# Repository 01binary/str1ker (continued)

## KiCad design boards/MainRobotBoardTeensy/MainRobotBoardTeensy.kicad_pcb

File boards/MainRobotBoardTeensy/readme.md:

# Main Robot Board

A board that controls robot head & body and measures voltage/current/battery charge.

+ Head Pan/Tilt
+ Torso Pan/Tilt
+ Mouth Movement
+ Voltage and Current Sensing

## Modules

The following components are placed onto the board as modules:

|Module|Function|
|-|-|
|[Teensy 4.1](https://www.sparkfun.com/teensy-4-1.html)|[ROS](https://www.ros.org/) Node|
|[ACS37220 Current Sensor 100A](https://www.pololu.com/product/5295)|Bus Current Sensing|
|[SSD1306 OLED Displays](https://www.amazon.com/dp/B00O2LKEW2)|Monochrome 0.96" 128x64 Voltage/Current/Power displays|
|[B10 1B4PG3Y2R](https://www.amazon.com/dp/B0C9QGMGFB)|Battery Charge Meter|
## Devices

The following external components are connected to the board via JST-XH locking connectors:

|Device|Function|
|-|-|
|[TB6600HG Stepper Motor Driver](https://www.amazon.com/dp/B01N6AIEQT)|Head Pan Motor|
|`4x` [Mini IBT Motor Driver](https://www.aliexpress.us/item/2251832603816751.html)|`2x` Head Tilt Motor Driver, `2x` Torso Tilt Motor Driver|
|`2x` Hollow Shaft Potentiometers|Head Tilt Encoder, Torso Tilt Encoder|
|[PerfectPass 56Kg Servo](https://www.amazon.com/dp/B09Y4NZJBJ)|Mouth Movement|
|[CPM-MCVC-3441S-RLN](https://teknic.com/model-info/CPM-MCVC-3441S-RLN/?model_voltage=75VDC)|Torso Pan Integrated Motor Driver

## Buses

|Bus|Device|Address
|-|-|-|
|`I2C`|SSD1306 voltage, current, and power meter displays|`0x3C`, `0x3D`|

## Pins

|Pin|Function
|-|-|
| `D14/A0`  | `ACS37220` Current Sensor `VOUT`
| `D15/A1`  | Head Tilt Potentiometer `SIG`
| `D16/A2`  | Torso Tilt Potentiometer `SIG`
| `D17/A3`  | Voltage Sense `SIG`
| `D19` | I2C `SCL` (SSD1306 x2)
| `D18` | I2C `SDA` (SSD1306 x2)
| `D0` | `TB6600` Head Pan Stepper Driver `EN`
| `D1` | `TB6600` Head Pan Stepper Driver `DIR`
| `D2` | `TB6600` Head Pan Stepper Driver `PUL`
| `D3` | `CPM-MCVC-3441S-RLN` Torso Motor `EN`
| `D4` | `CPM-MCVC-3441S-RLN` Torso Motor `DIR` (A)
| `D5` | `CPM-MCVC-3441S-RLN` Torso Motor `PWM` (B)
| `D7` | Head Tilt Motor Driver 1 `EN`
| `D8` | Head Tilt Motor Driver 2 `EN`
| `D20` | Torso Tilt Motor Driver 1 `EN`
| `D21` | Torso Tilt Motor Driver 2 `EN`
| `D9` | Head Tilt Motor Driver 1 `LPWM`
| `D10` | Head Tilt Motor Driver 1 `RPWM`
| `D11` | Head Tilt Motor Driver 2 `LPWM`
| `D12` | Head Tilt Motor Driver 2 `RPWM`
| `D22` | Torso Tilt Motor Driver 1 `LPWM`
| `D23` | Torso Tilt Motor Driver 1 `RPWM`
| `D28` | Torso Tilt Motor Driver 2 `LPWM`
| `D29` | Torso Tilt Motor Driver 2 `RPWM`
| `D24` | Battery Level Meter `LED1` (Lowest Charge)
| `D25` | Battery Level Meter `LED2`
| `D26` | Battery Level Meter `LED3`
| `D27` | Battery Level Meter `LED4`
| `D30` | Battery Level Meter `LED5`
| `D31` | Battery Level Meter `LED6`
| `D32` | Battery Level Meter `LED7`
| `D33` | Battery Level Meter `LED8`
| `D34` | Battery Level Meter `LED9`
| `D35` | Battery Level Meter `LED10` (Highest Charge)
| `D36` | PerfectPass Servo `SIG`

## ROS Interface

The main-board Teensy is a rosserial node at `115200` baud. Its USB serial
port is reserved for ROS framing; the sketch does not print diagnostic text.

|Topic|Type|Direction|Rate / behavior|
|-|-|-|-|
|`main/command`|`str1ker/MainCommand`|Subscribe|Normalized `[-1, 1]` velocity commands for head pan/tilt and torso pan/tilt, plus mouth position in degrees. Motion stops if commands are absent for 500 ms.|
|`main/power`|`str1ker/PowerState`|Publish|Voltage (V), current (A), and power (W), at 10 Hz.|
|`main/battery`|`sensor_msgs/BatteryState`|Publish|LiFePO4 pack voltage, current, and estimated charge percentage, at 10 Hz.|
|`main/joint_states`|`sensor_msgs/JointState`|Publish|`head_tilt_joint`, `torso_tilt_joint`, and `mouth_joint` positions, at 10 Hz.|

The mouth servo is commanded to 90 degrees during startup. The two
potentiometer positions are currently normalized to `[0, 1]`; calibrate their
ADC endpoints and angular ranges in the firmware before treating them as
radians in a robot model. Head pan and torso pan are omitted from feedback
because this board has no position sensors for those axes.

## Bill of Materials

|Component|Description|
|-|-|
|[150080BS75000](https://www.digikey.com/en/products/detail/w%C3%BCrth-elektronik/)|Blue LED for `LPWM`/`RPWM` activity|
|[XL-1608SURC-06](https://www.lcsc.com/product-detail/C965799.html)|Red LED for `EN` status|
|[RC0603FR-0747RL](https://www.digikey.com/en/products/detail/yageo/rc0603fr-0747rl/727252)|`47R` Series Resistor (PWM channels)|
|[RC0603FR-07150RL](https://www.digikey.com/en/products/detail/yageo/RC0603FR-07150RL/726958)|`150R` Blue LED Resistor|
|[RC0603FR-07470RL](https://www.digikey.com/en/products/detail/yageo/RC0603FR-07470RL/727256)|`470R` Red LED and Battery Bar Segment Resistor|
|[RCG06031K00FKEA](https://www.digikey.com/en/products/detail/vishay-dale/rcg06031k00fkea/4172389)|`1K` Red LED Resistor|
|[RC0603FR-072K2L](https://www.digikey.com/en/products/detail/yageo/RC0603FR-072K2L/727016)|`2.2K` Series Resistor (ADC channels)|
|[CRCW060310K0FKEA](https://www.digikey.com/en/products/detail/vishay-dale/crcw060310k0fkea/1174782)|`10K` Pull-Down Resistor (PWM channels)|
|[0603WAF2202T5E](https://jlcpcb.com/partdetail/32812-0603WAF2202T5E/C31850)|`22K` Voltage Sense Divider Resistor|
|[CRCW0603100KFKEA](https://www.digikey.com/en/products/detail/vishay-dale/crcw0603100kfkea/1174896)|`100K` Pull-Dowh Resistor|
|[CL10B473KB8NNNC](https://www.digikey.com/en/products/detail/samsung-electro-mechanics/cl10b473kb8nnnc/3886721)|`47nF` Capacitor (ADC channels)|
|[SN74HC08DR](https://www.digikey.com/en/products/detail/texas-instruments/sn74hc08dr/276834)|IC Gate|
|[B10 1B4PG3Y2R](https://www.amazon.com/dp/B0C9QGMGFB)|LED Light Bar (Red/Blue/Green) with `DIP-20` Socket (Battery Charge Meter)|
|[AO3400A](https://www.digikey.com/en/products/detail/alpha-omega-semiconductor-inc/ao3400a/1855772)|LED Transistor|
|[TLC555CDR](https://www.digikey.com/en/products/detail/texas-instruments/tlc555cdr/276979)|555 Timer|
|[RC0603FR-07360KL](https://www.digikey.com/en/products/detail/yageo/rc0603fr-07360kl/727183)|555 Timer Resistor `360K`|
|[CC0603JRX7R7BB105](https://www.digikey.com/en/products/detail/yageo/CC0603JRX7R7BB105/7164369)|555 Timer Capacitor `1uF`|
|[C0402C103J4RACTU](https://www.digikey.com/en/products/detail/kemet/C0402C103J4RACTU/411041)|555 Timer Capacitor `0.01uF`|
|[CC0603KRX7R9BB104](https://www.digikey.com/en/products/detail/yageo/cc0603krx7r9bb104/2103082)|`100nF` Voltage Sense Capacitor|
|[74HCT125D,653](https://www.digikey.com/en/products/detail/nexperia-usa-inc/74hct125d-653/763113)|`3.3V` to `5V` Level Shifter|
|[JST_XH_B3B-XH-A](https://www.digikey.com/en/products/detail/jst-sales-america-inc/b3b-xh-a/1651046)|3-pin male receptacle for Head Tilt Potentiometer, Torso Tilt Potentiometer (`3V3`, `SIG`, `GND`), Head Tilt Driver, Torso Tilt Drivers (`LPWM`, `RPWM`, `EN`)|
|[JST_XH_B4B-XH-A](https://www.digikey.com/en/products/detail/jst-sales-america-inc/b4b-xh-a/1651047)|4-pin male receptacle for `TB6600` Driver (`3V3`, `PUL`, `DIR`, `ENA`)|
|[Molex 0702460802](https://www.digikey.com/en/products/detail/molex/0702460802/760180)|2-row 4-pin male receptacle for `CPM-MCVC-3441S-RLN` Driver (`EN+`, `EN-`, `A+`, `A-`, `B+`, `B-`, `ST+`, `ST-`)|
|[Teensy 4.1](https://www.sparkfun.com/teensy-4-1.html)|Teensy 4.1 without Headers|
|[ICM-648-1-GT-HT](https://www.digikey.com/en/products/detail/adam-tech/ICM-648-1-GT-HT/9832918)|Teensy IC DIP Socket, 48P|
|[Needle Headers](https://www.amazon.com/dp/B09WH8N3HX)|Teensy Needle Headers for DIP Socket|
|[ACS37220](https://www.pololu.com/product/5295)|Current Sensor `100A`, `3.3V` Logic|
|2x [SSD1306](https://www.amazon.com/dp/B00O2LKEW2)|Monochrome I2C OLED Displays `3.3V`|

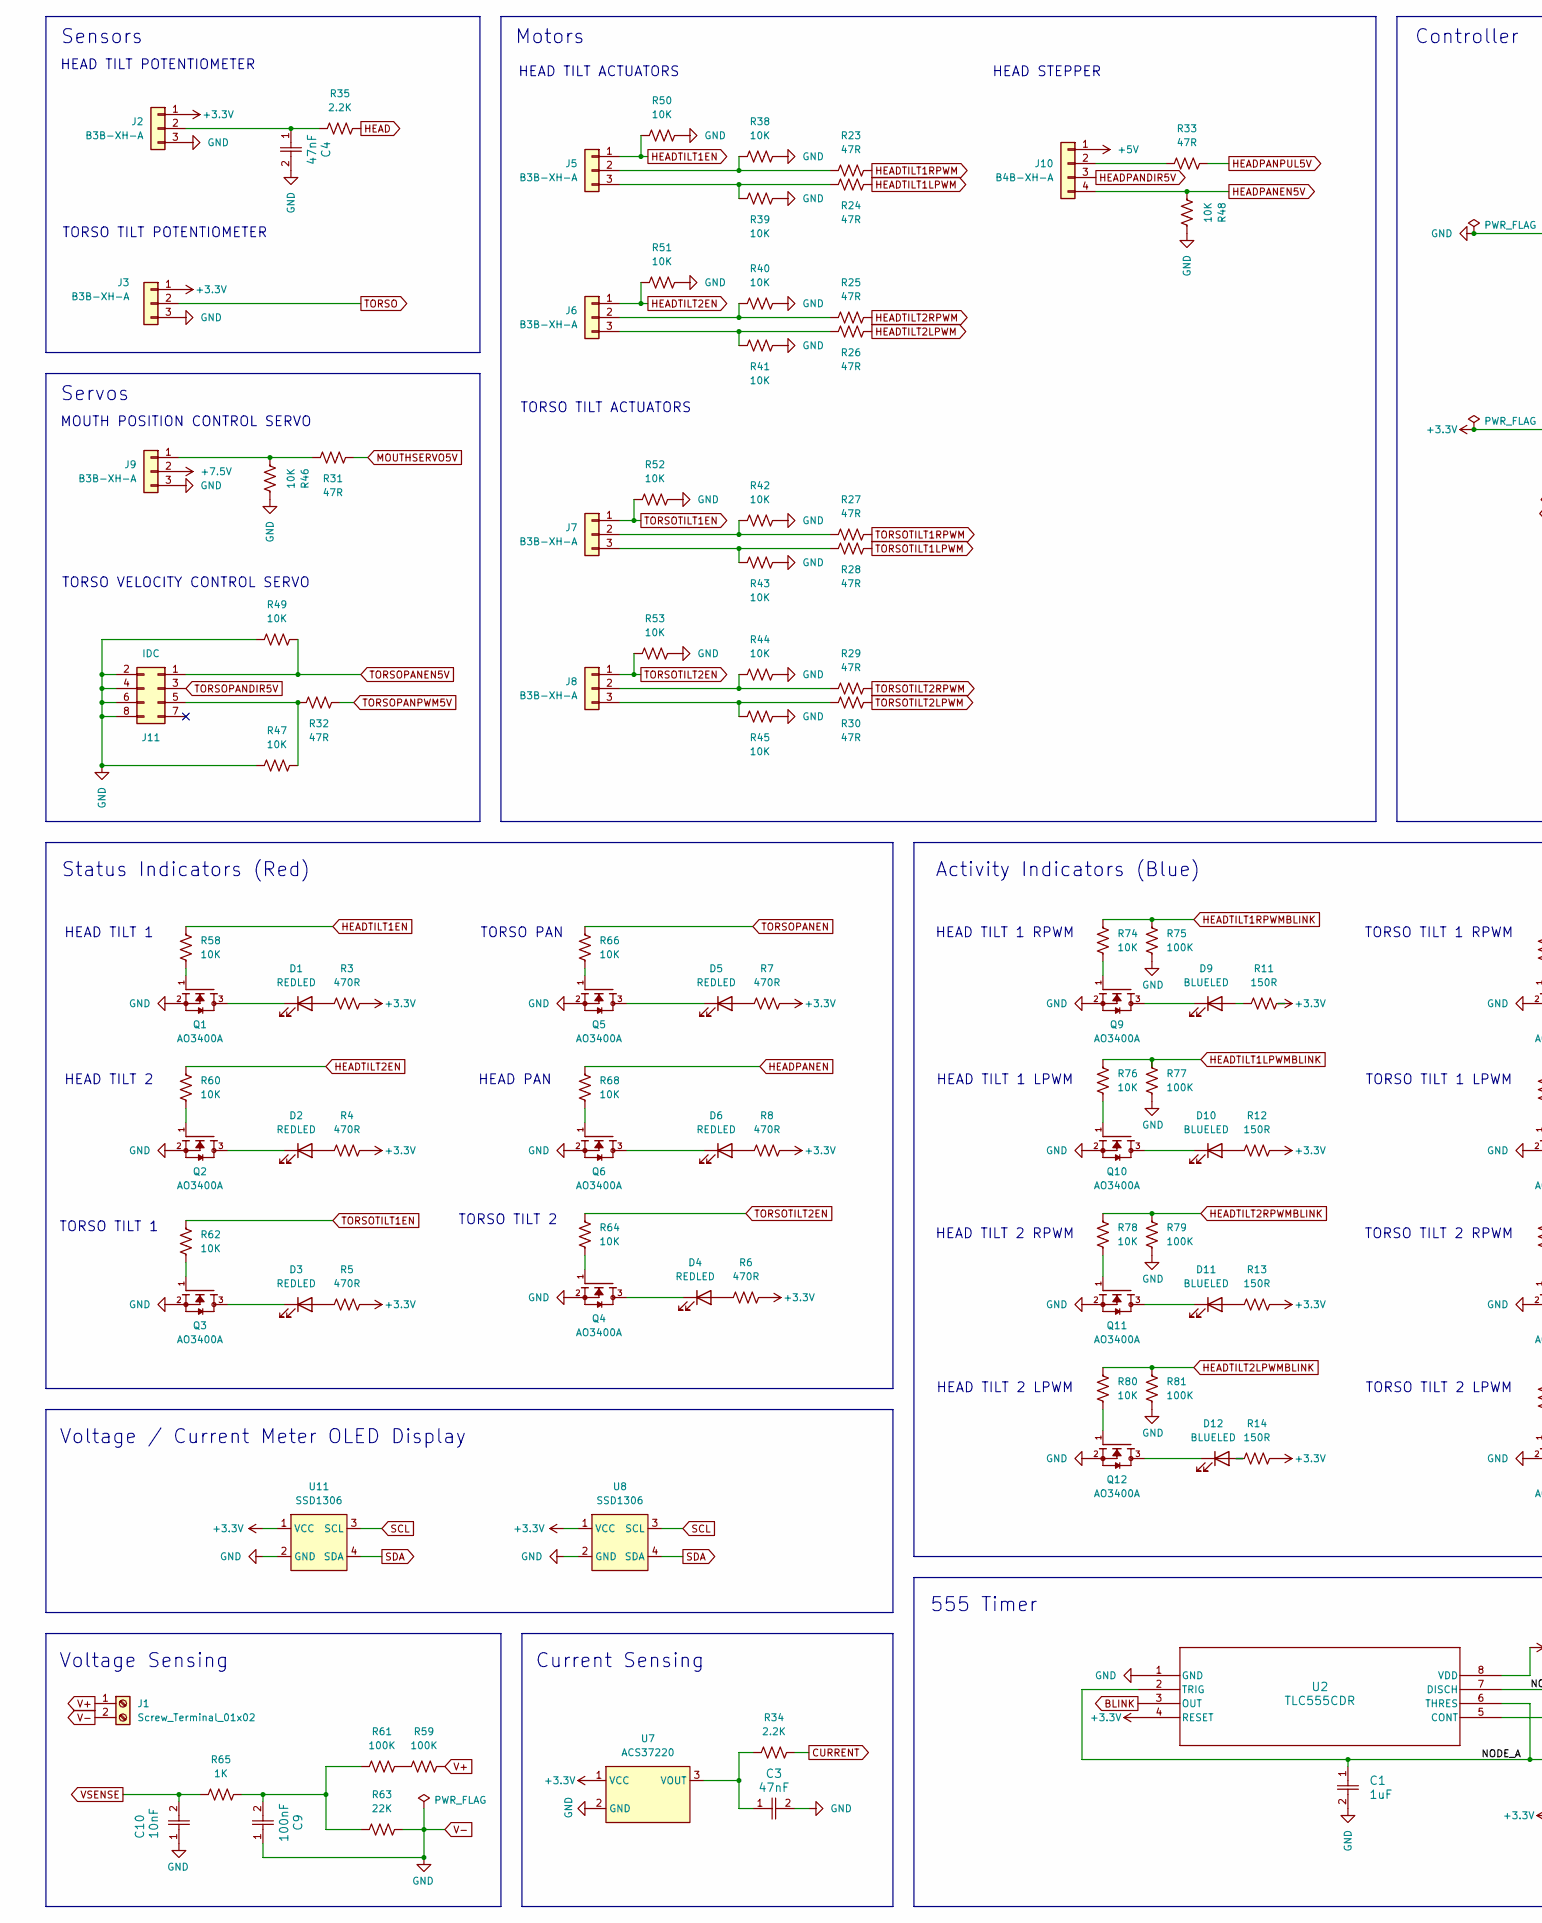
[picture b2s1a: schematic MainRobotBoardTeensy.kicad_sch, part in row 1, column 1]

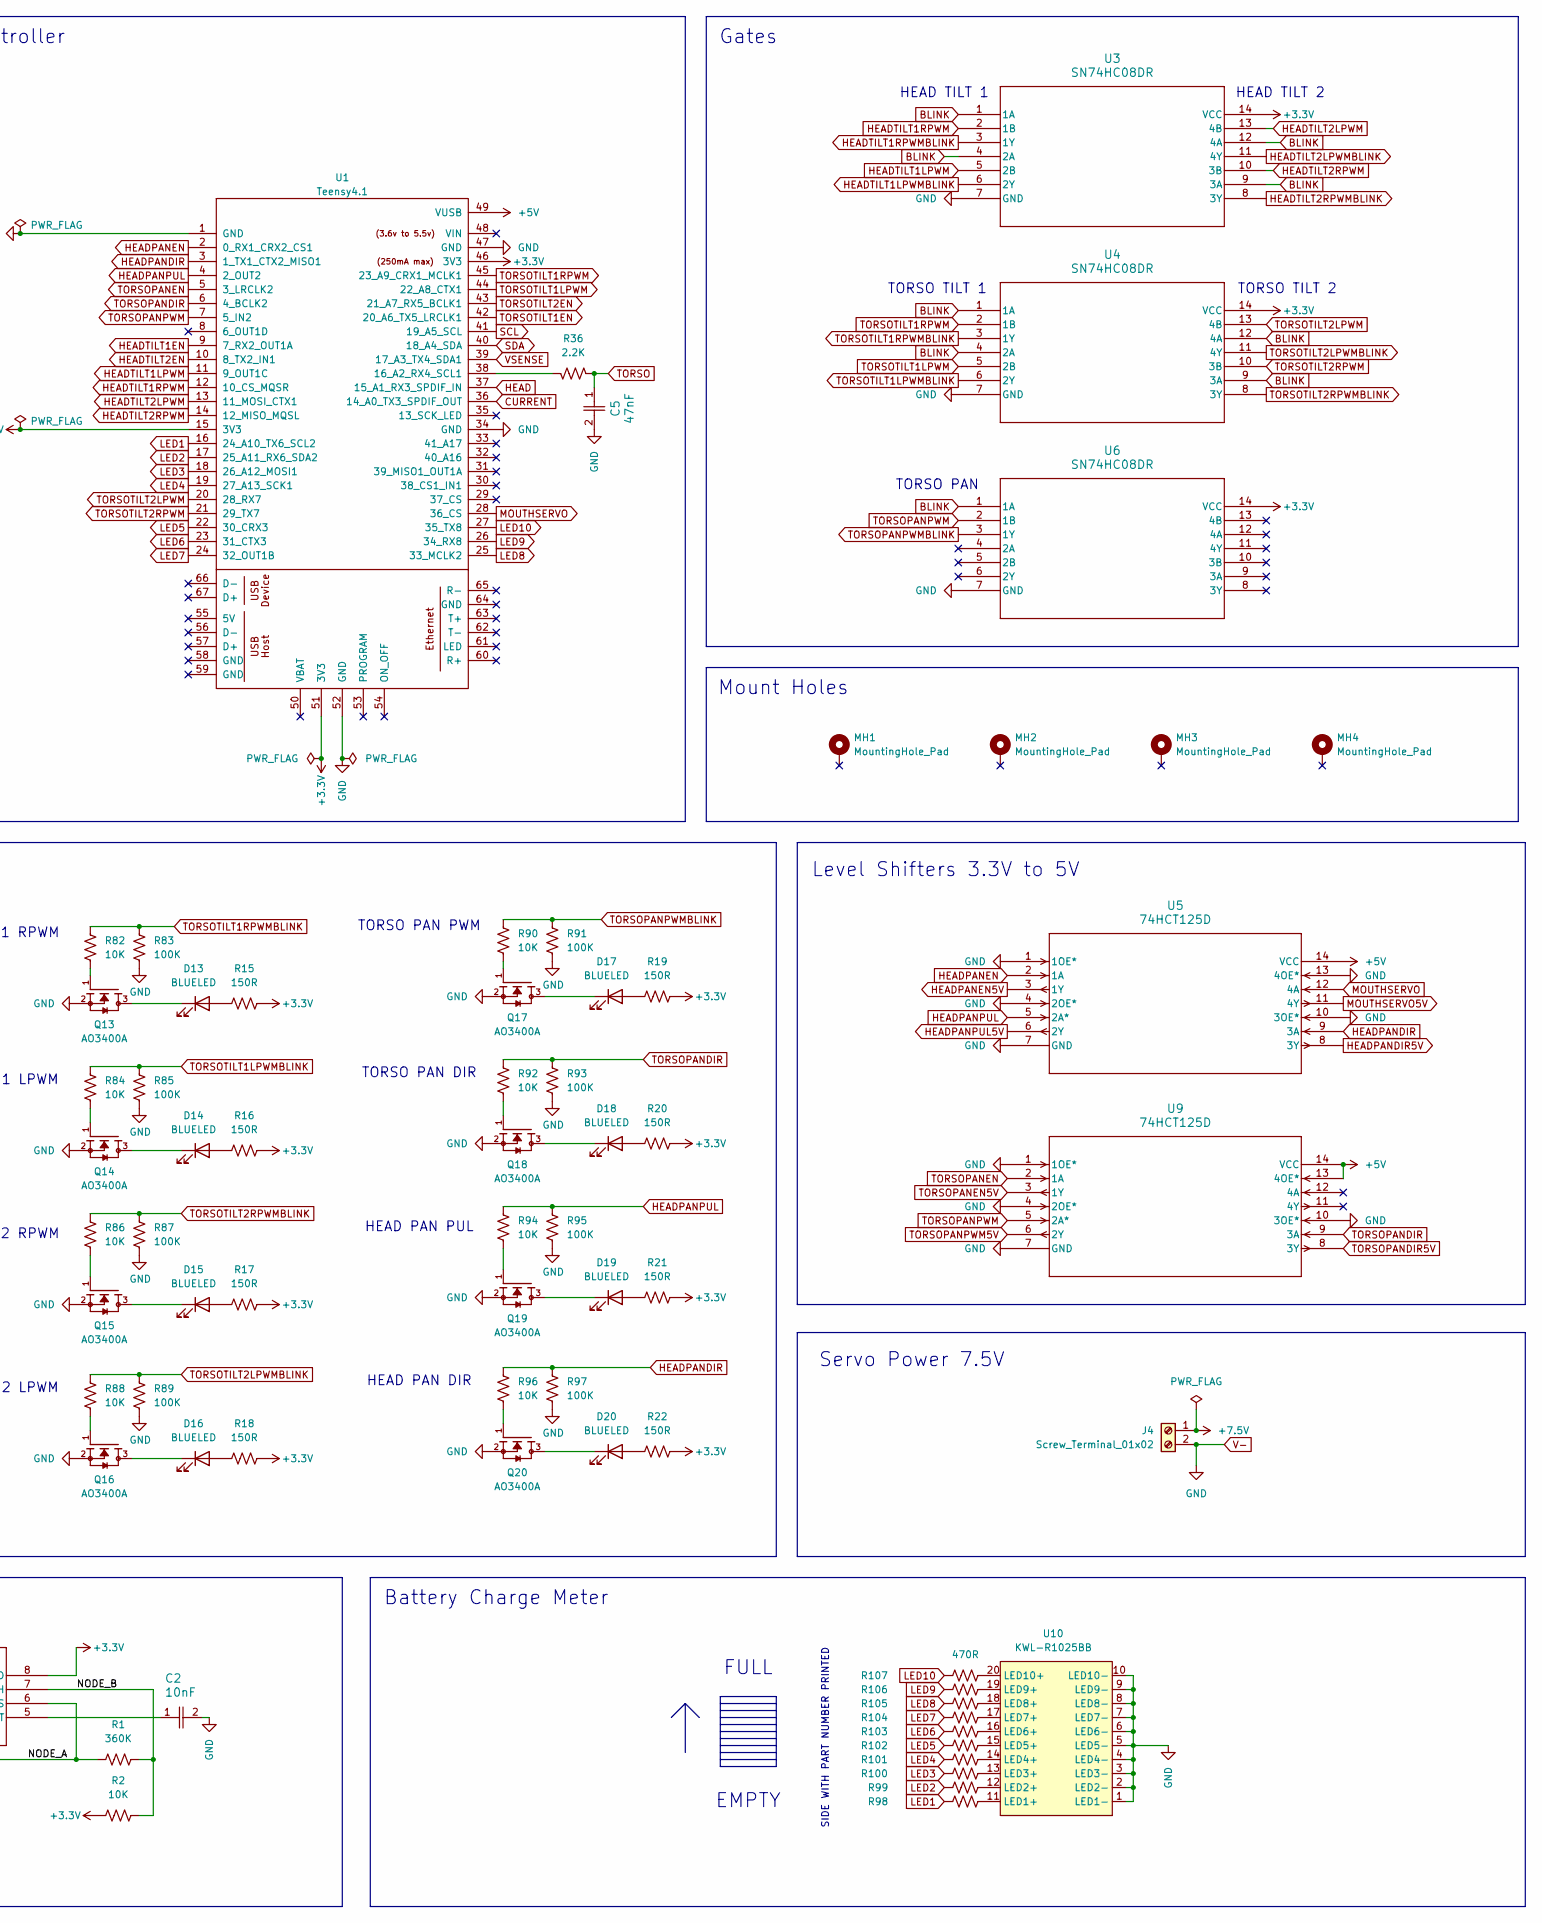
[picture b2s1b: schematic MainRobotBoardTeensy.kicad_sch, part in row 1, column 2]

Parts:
C1: 1uF; CC0603JRX7R7BB105; LCSC C519560
C2, C10: 10nF; C0402C103J4RACTU; LCSC C152817
C3, C4, C5: 47nF; CAPC1608X90N; LCSC C1622
C9: 100nF; CC0603KRX7R9BB104; LCSC C14663
D1, D2, D3, D4, D5, D6: REDLED; XL-1608SURC-06; LCSC C965799
D9, D10, D11, D12, D13, D14, D15, D16, D17, D18, D19, D20: BLUELED; 150080BS75000_Modified; LCSC C6067133
J1, J4: Screw_Terminal_01x02; TerminalBlock_Phoenix_MKDS-1,5-2-5.08_1x02_P5.08mm_Horizont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
J2, J3, J5, J6, J7, J8, J9: B3B-XH-A; JST_XH_B3B-XH-A_1x03_P2.50mm_Vertical
J10: B4B-XH-A; JST_XH_B4B-XH-A_1x04_P2.50mm_Vertical
J11: IDC; IDC-Header_2x04_P2.54mm_Vertical
MH1, MH2, MH3, MH4: MountingHole_Pad; MountingHole_3.2mm_M3_ISO7380_Pad
Q1, Q2, Q3, Q4, Q5, Q6, Q9, Q10, Q11, Q12, Q13, Q14, Q15, Q16, Q17, Q18, Q19, Q20: AO3400A; LCSC C20917
R1: 360K; RC0603FR-07360KL; LCSC C137740
R2, R38, R39, R40, R41, R42, R43, R44, R45, R46, R47, R48, R49, R50, R51, R52, R53, R58, R60, R62, R64, R66, R68, R74, R76, R78, R80, R82, R84, R86, R88, R90, R92, R94, R96: 10K; CRCW060310K0FKEA; LCSC C844918
R3, R4, R5, R6, R7, R8, R98, R99, R100, R101, R102, R103, R104, R105, R106, R107: 470R; RC0603FR-07470RL; LCSC C114669
R11, R12, R13, R14, R15, R16, R17, R18, R19, R20, R21, R22: 150R; RESC1607X60N; LCSC C114608
R23, R24, R25, R26, R27, R28, R29, R30, R31, R32, R33: 47R; RESC1608X55; LCSC C114623
R34, R35, R36: 2.2K; RC0603FR-072K2L; LCSC C114662
R59, R61, R75, R77, R79, R81, R83, R85, R87, R89, R91, R93, R95, R97: 100K; CRCW0603100KFKEA; LCSC C844916
R63: 22K; 0603WAF2202T5E; LCSC C31850
R65: 1K; RCG06031K00FKEA; LCSC C4264491
U1: Teensy4.1; Teensy41
U2: TLC555CDR; LCSC C6986
U3, U4, U6: SN74HC08DR; LCSC C337768
U5, U9: 74HCT125D
U7: ACS37220
U8, U11: SSD1306
U10: KWL-R1025BB

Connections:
+3.3V: J2.1, J3.1, R2.1, R3.2, R4.2, R5.2, R6.2, R7.2, R8.2, R11.2, R12.2, R13.2, R14.2, R15.2, R16.2, R17.2, R18.2, R19.2, R20.2, R21.2, R22.2, U1.15 (3V3), U1.46 (3V3), U1.51 (3V3), U2.4 (RESET), U2.8 (VDD), U3.14 (VCC), U4.14 (VCC), U6.14 (VCC), U7.1 (VCC), U8.1 (VCC), U11.1 (VCC)
+5V: J10.1, U1.49 (VUSB), U5.14 (VCC), U9.13 (4OE*), U9.14 (VCC)
+7.5V: J4.1, J9.2
/NODE_A: C1.1, R1.1, U2.2 (TRIG), U2.6 (THRES)
/NODE_B: R1.2, R2.2, U2.7 (DISCH)
BLINK: U2.3 (OUT), U3.1 (1A), U3.4 (2A), U3.9 (3A), U3.12 (4A), U4.1 (1A), U4.4 (2A), U4.9 (3A), U4.12 (4A), U6.1 (1A)
CURRENT: R34.2, U1.36 (14_A0_TX3_SPDIF_OUT)
HEAD: R35.2, U1.37 (15_A1_RX3_SPDIF_IN)
HEADPANDIR: R96.1, R97.1, U1.3 (1_TX1_CTX2_MISO1), U5.9 (3A)
HEADPANDIR5V: J10.3, U5.8 (3Y)
HEADPANEN: R68.1, U1.2 (0_RX1_CRX2_CS1), U5.2 (1A)
HEADPANEN5V: J10.4, R48.1, U5.3 (1Y)
HEADPANPUL: R94.1, R95.1, U1.4 (2_OUT2), U5.5 (2A*)
HEADPANPUL5V: R33.2, U5.6 (2Y)
HEADTILT1EN: J5.1, R50.1, R58.1, U1.9 (7_RX2_OUT1A)
HEADTILT1LPWM: R24.2, U1.11 (9_OUT1C), U3.5 (2B)
HEADTILT1LPWMBLINK: R76.1, R77.1, U3.6 (2Y)
HEADTILT1RPWM: R23.2, U1.12 (10_CS_MQSR), U3.2 (1B)
HEADTILT1RPWMBLINK: R74.1, R75.1, U3.3 (1Y)
HEADTILT2EN: J6.1, R51.1, R60.1, U1.10 (8_TX2_IN1)
HEADTILT2LPWM: R26.2, U1.13 (11_MOSI_CTX1), U3.13 (4B)
HEADTILT2LPWMBLINK: R80.1, R81.1, U3.11 (4Y)
HEADTILT2RPWM: R25.2, U1.14 (12_MISO_MQSL), U3.10 (3B)
HEADTILT2RPWMBLINK: R78.1, R79.1, U3.8 (3Y)
LED1: R98.2, U1.16 (24_A10_TX6_SCL2)
LED2: R99.2, U1.17 (25_A11_RX6_SDA2)
LED3: R100.2, U1.18 (26_A12_MOSI1)
LED4: R101.2, U1.19 (27_A13_SCK1)
LED5: R102.2, U1.22 (30_CRX3)
LED6: R103.2, U1.23 (31_CTX3)
LED7: R104.2, U1.24 (32_OUT1B)
LED8: R105.2, U1.25 (33_MCLK2)
LED9: R106.2, U1.26 (34_RX8)
LED10: R107.2, U1.27 (35_TX8)
MOUTHSERVO: U1.28 (36_CS), U5.12 (4A)
MOUTHSERVO5V: R31.2, U5.11 (4Y)
unnamed: C9.2, R61.1, R63.1, R65.2
unnamed: D1.2 (A), R3.1
unnamed: D1.1 (K), Q1.3
unnamed: D2.2 (A), R4.1
unnamed: D2.1 (K), Q2.3
unnamed: D3.2 (A), R5.1
unnamed: D3.1 (K), Q3.3
unnamed: D4.2 (A), R6.1
unnamed: D4.1 (K), Q4.3
unnamed: D5.2 (A), R7.1
unnamed: D5.1 (K), Q5.3
unnamed: D6.2 (A), R8.1
unnamed: D6.1 (K), Q6.3
unnamed: D9.2 (A), R11.1
unnamed: D9.1 (K), Q9.3
unnamed: D10.2 (A), R12.1
unnamed: D10.1 (K), Q10.3
unnamed: D11.2 (A), R13.1
unnamed: D11.1 (K), Q11.3
unnamed: D12.2 (A), R14.1
unnamed: D12.1 (K), Q12.3
unnamed: D13.2 (A), R15.1
unnamed: D13.1 (K), Q13.3
unnamed: D14.2 (A), R16.1
unnamed: D14.1 (K), Q14.3
unnamed: D15.2 (A), R17.1
unnamed: D15.1 (K), Q15.3
unnamed: D16.2 (A), R18.1
unnamed: D16.1 (K), Q16.3
unnamed: D17.2 (A), R19.1
unnamed: D17.1 (K), Q17.3
unnamed: D18.2 (A), R20.1
unnamed: D18.1 (K), Q18.3
unnamed: D19.2 (A), R21.1
unnamed: D19.1 (K), Q19.3
unnamed: D20.2 (A), R22.1
unnamed: D20.1 (K), Q20.3
unnamed: C4.1, J2.2, R35.1
unnamed: J5.2, R23.1, R38.1
unnamed: J5.3, R24.1, R39.1
unnamed: J6.2, R25.1, R40.1
unnamed: J6.3, R26.1, R41.1
unnamed: J7.2, R27.1, R42.1
unnamed: J7.3, R28.1, R43.1
unnamed: J8.2, R29.1, R44.1
unnamed: J8.3, R30.1, R45.1
unnamed: J9.1, R31.1, R46.1
unnamed: J10.2, R33.1
unnamed: J11.5, R32.1, R47.1
unnamed: Q1.1, R58.2
unnamed: Q2.1, R60.2
unnamed: Q3.1, R62.2
unnamed: Q4.1, R64.2
unnamed: Q5.1, R66.2
unnamed: Q6.1, R68.2
unnamed: Q9.1, R74.2
unnamed: Q10.1, R76.2
unnamed: Q11.1, R78.2
unnamed: Q12.1, R80.2
unnamed: Q13.1, R82.2
unnamed: Q14.1, R84.2
unnamed: Q15.1, R86.2
unnamed: Q16.1, R88.2
unnamed: Q17.1, R90.2
unnamed: Q18.1, R92.2
unnamed: Q19.1, R94.2
unnamed: Q20.1, R96.2
unnamed: R59.1, R61.2
unnamed: R36.2, U1.38 (16_A2_RX4_SCL1)
unnamed: C2.1, U2.5 (CONT)
unnamed: C3.1, R34.1, U7.3 (VOUT)
unnamed: R98.1, U10.11 (LED1+)
unnamed: R99.1, U10.12 (LED2+)
unnamed: R100.1, U10.13 (LED3+)
unnamed: R101.1, U10.14 (LED4+)
unnamed: R102.1, U10.15 (LED5+)
unnamed: R103.1, U10.16 (LED6+)
unnamed: R104.1, U10.17 (LED7+)
unnamed: R105.1, U10.18 (LED8+)
unnamed: R106.1, U10.19 (LED9+)
unnamed: R107.1, U10.20 (LED10+)
SCL: U1.41 (19_A5_SCL), U8.3 (SCL), U11.3 (SCL)
SDA: U1.40 (18_A4_SDA), U8.4 (SDA), U11.4 (SDA)
TORSO: C5.1, J3.2, R36.1
TORSOPANDIR: R92.1, R93.1, U1.6 (4_BCLK2), U9.9 (3A)
TORSOPANDIR5V: J11.3, U9.8 (3Y)
TORSOPANEN: R66.1, U1.5 (3_LRCLK2), U9.2 (1A)
TORSOPANEN5V: J11.1, R49.2, U9.3 (1Y)
TORSOPANPWM: U1.7 (5_IN2), U6.2 (1B), U9.5 (2A*)
TORSOPANPWM5V: R32.2, U9.6 (2Y)
TORSOPANPWMBLINK: R90.1, R91.1, U6.3 (1Y)
TORSOTILT1EN: J7.1, R52.1, R62.1, U1.42 (20_A6_TX5_LRCLK1)
TORSOTILT1LPWM: R28.2, U1.44 (22_A8_CTX1), U4.5 (2B)
TORSOTILT1LPWMBLINK: R84.1, R85.1, U4.6 (2Y)
TORSOTILT1RPWM: R27.2, U1.45 (23_A9_CRX1_MCLK1), U4.2 (1B)
TORSOTILT1RPWMBLINK: R82.1, R83.1, U4.3 (1Y)
TORSOTILT2EN: J8.1, R53.1, R64.1, U1.43 (21_A7_RX5_BCLK1)
TORSOTILT2LPWM: R30.2, U1.20 (28_RX7), U4.13 (4B)
TORSOTILT2LPWMBLINK: R88.1, R89.1, U4.11 (4Y)
TORSOTILT2RPWM: R29.2, U1.21 (29_TX7), U4.10 (3B)
TORSOTILT2RPWMBLINK: R86.1, R87.1, U4.8 (3Y)
V+: J1.1, R59.2
V-: C1.2, C2.2, C3.2, C4.2, C5.2, C9.1, C10.1, J1.2, J2.3, J3.3, J4.2, J9.3, J11.2, J11.4, J11.6, J11.8, Q1.2, Q2.2, Q3.2, Q4.2, Q5.2, Q6.2, Q9.2, Q10.2, Q11.2, Q12.2, Q13.2, Q14.2, Q15.2, Q16.2, Q17.2, Q18.2, Q19.2, Q20.2, R38.2, R39.2, R40.2, R41.2, R42.2, R43.2, R44.2, R45.2, R46.2, R47.2, R48.2, R49.1, R50.2, R51.2, R52.2, R53.2, R63.2, R75.2, R77.2, R79.2, R81.2, R83.2, R85.2, R87.2, R89.2, R91.2, R93.2, R95.2, R97.2, U1.1 (GND), U1.34 (GND), U1.47 (GND), U1.52 (GND), U2.1 (GND), U3.7 (GND), U4.7 (GND), U5.1 (1OE*), U5.4 (2OE*), U5.7 (GND), U5.10 (3OE*), U5.13 (4OE*), U6.7 (GND), U7.2 (GND), U8.2 (GND), U9.1 (1OE*), U9.4 (2OE*), U9.7 (GND), U9.10 (3OE*), U10.1 (LED1-), U10.2 (LED2-), U10.3 (LED3-), U10.4 (LED4-), U10.5 (LED5-), U10.6 (LED6-), U10.7 (LED7-), U10.8 (LED8-), U10.9 (LED9-), U10.10 (LED10-), U11.2 (GND)
VSENSE: C10.2, R65.1, U1.39 (17_A3_TX4_SDA1)

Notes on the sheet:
HEAD TILT ACTUATORS
TORSO PAN
HEAD PAN DIR
Gates
Battery Charge Meter
TORSO TILT 1 RPWM
HEAD TILT 2
TORSO TILT 2
HEAD TILT 1
TORSO PAN PWM
TORSO PAN DIR
Sensors
Motors
Mount Holes
TORSO TILT 1 LPWM
Level Shifters 3.3V to 5V
555 Timer
Controller
Voltage Sensing
HEAD TILT 1 RPWM
TORSO TILT ACTUATORS
FULL
Activity Indicators (Blue)
TORSO TILT 1
Voltage / Current Meter OLED Display
TORSO VELOCITY CONTROL SERVO
HEAD PAN
Status Indicators (Red)
Servos
HEAD TILT POTENTIOMETER
Current Sensing
EMPTY
SIDE WITH PART NUMBER PRINTED
HEAD TILT 2 LPWM
Servo Power 7.5V
TORSO TILT 2 LPWM
TORSO TILT POTENTIOMETER
MOUTH POSITION CONTROL SERVO
HEAD STEPPER
HEAD TILT 1 LPWM

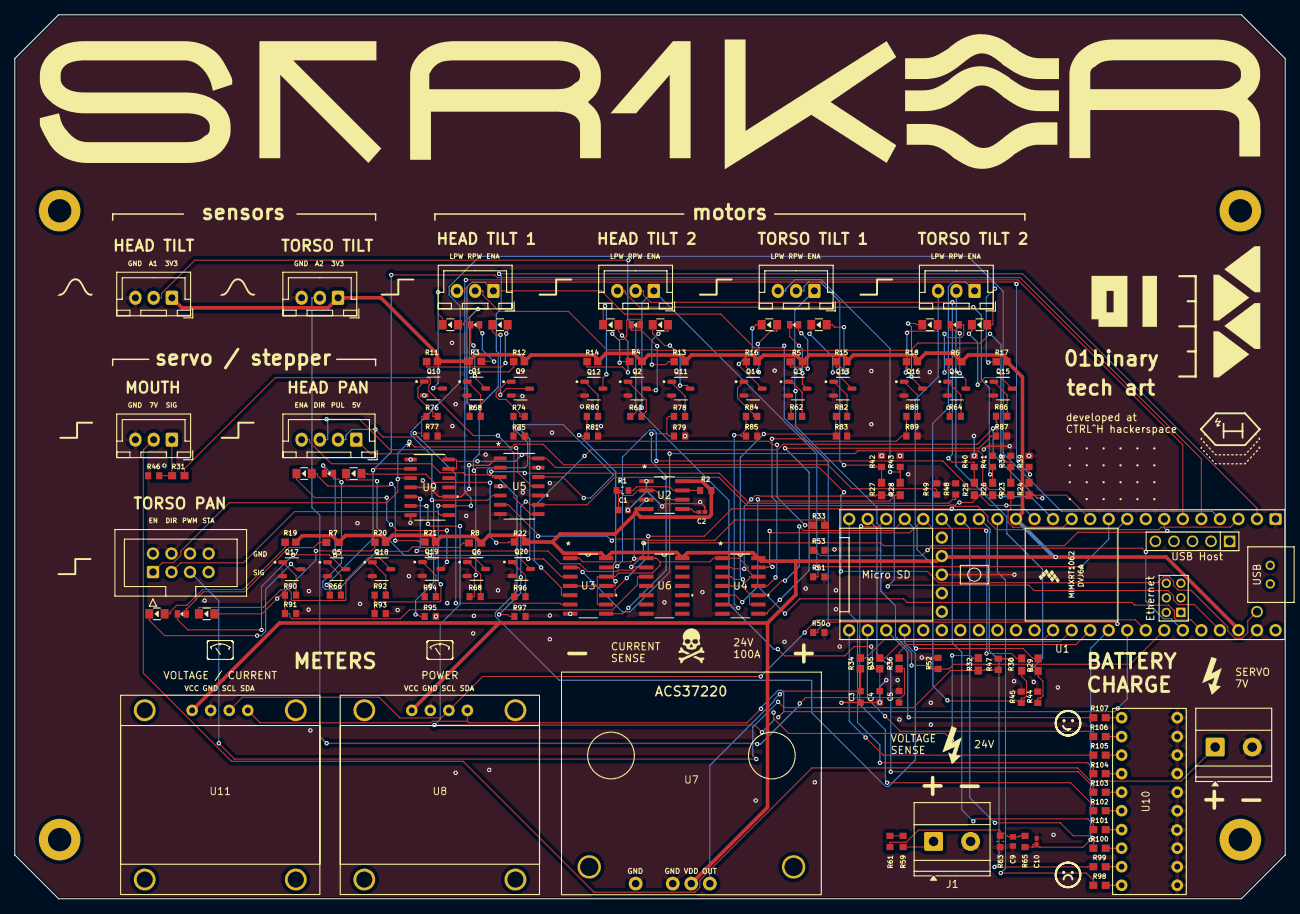
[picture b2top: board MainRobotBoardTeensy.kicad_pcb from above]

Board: 2 copper layers, 174.0 x 121.1 mm, 163 parts (0 on the bottom side), 140 nets.

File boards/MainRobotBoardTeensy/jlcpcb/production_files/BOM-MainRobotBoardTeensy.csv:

Comment,Designator,Footprint,LCSC,Quantity
100K,"R59,R61,R75,R77,R79,R81,R83,R85,R87,R89,R91,R93,R95,R97",CRCW0603100KFKEA,C844916,14
100nF,C9,CC0603KRX7R9BB104,C14663,1
10K,"R2,R38,R39,R40,R41,R42,R43,R44,R45,R46,R47,R48,R49,R50,R51,R52,R53,R58,R60,R62,R64,R66,R68,R74,R76,R78,R80,R82,R84,R86,R88,R90,R92,R94,R96",CRCW060310K0FKEA,C844918,35
10nF,"C10,C2",C0402C103J4RACTU,C152817,2
150R,"R11,R12,R13,R14,R15,R16,R17,R18,R19,R20,R21,R22",RESC1607X60N,C114608,12
1K,R65,RCG06031K00FKEA,C4264491,1
1uF,C1,CC0603JRX7R7BB105,C519560,1
2.2K,"R34,R35,R36",RC0603FR-072K2L,C114662,3
22K,R63,0603WAF2202T5E,C31850,1
360K,R1,RC0603FR-07360KL,C137740,1
470R,"R100,R101,R102,R103,R104,R105,R106,R107,R3,R4,R5,R6,R7,R8,R98,R99",RC0603FR-07470RL,C114669,16
47R,"R23,R24,R25,R26,R27,R28,R29,R30,R31,R32,R33",RESC1608X55,C114623,11
47nF,"C3,C4,C5",CAPC1608X90N,C1622,3
AO3400A,"Q1,Q10,Q11,Q12,Q13,Q14,Q15,Q16,Q17,Q18,Q19,Q2,Q20,Q3,Q4,Q5,Q6,Q9",AO3400A,C20917,18
BLUELED,"D10,D11,D12,D13,D14,D15,D16,D17,D18,D19,D20,D9",150080BS75000_Modified,C6067133,12
REDLED,"D1,D2,D3,D4,D5,D6",XL-1608SURC-06,C965799,6
SN74HC08DR,"U3,U4,U6",SN74HC08DR,C337768,3
TLC555CDR,U2,TLC555CDR,C6986,1
74HCT125D,U9,74HCT125D,,1
Teensy4.1,U1,Teensy41,,1
74HCT125D,U5,74HCT125D,,1
Screw_Terminal_01x02,J4,"TerminalBlock_Phoenix_MKDS-1,5-2-5.08_1x02_P5.08mm_Horizontal",,1

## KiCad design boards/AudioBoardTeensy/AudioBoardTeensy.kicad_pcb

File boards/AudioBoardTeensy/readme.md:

# Audio Board

Displays audio waveform and level meter when the robot talks.

## Components

The following components are used:

|Component|Function|
|-|-|
|[Teensy 4.0](https://www.sparkfun.com/teensy-4-0.html)|MCU
|[SSD1309 OLED Display](https://www.dfrobot.com/product-2521.html)|Audio waveform display
|[Adafruit Sequins](https://www.adafruit.com/product/1792)|Audio level metering

## Buses

|Bus|Devices
|-|-|
|`SPI`|SSD1309

## Pins

|Pin|Function|
|-|-|
|`A0` | Audio input from Voltage Divider
|`D13`| OLED Display `SCK`
|`D12`| OLED Display `DC` (`MISO`)
|`D11`| OLED Display `MOSI`
|`D0` | OLED Display `CS`
|`D1` | OLED Display Reset
|`D2` | LED 1
|`D3` | LED 2
|`D4` | LED 3
|`D5` | LED 4
|`D6` | LED 5

Only a single pin from the TRRS audio jack (stereo audio + mono mic) is used as the audio signal for this board:

|Jack Pin|Description|Function
|-|-|-|
|`4`|Tip|Left audio channel output to Voltage Divider
|`3`|Ring 1|Right audio channel (unconnected)
|`2`|Ring 2|`GND`
|`1`|Sleeve|Mic (unconnected)

> This audio jack was used because it's more commonly in stock by various manufacturers than mono audio jacks or stereo audio jacks with no mic.

## Bill of Materials

|Component|Description|
|-|-|
|[CRCW0603100KFKEA](https://www.digikey.com/en/products/detail/vishay-dale/crcw0603100kfkea/1174896)|Voltage Divider Resistor `100K`
|[CL10A106KP8NNNC](https://www.digikey.com/en/products/detail/samsung-electro-mechanics/cl10a106kp8nnnc/3886850)|Voltage Bias Capacitor `10uF`
|[0603WAF2001T5E](https://www.lcsc.com/product-detail/C22975.html)|Pull-Down Resistor `2K`
|[RCG06031K00FKEA](https://www.digikey.com/en/products/detail/vishay-dale/rcg06031k00fkea/4172389)|Current-Limiting Resistor `1K`
|[54-00174](https://www.digikey.com/en/products/detail/tensility-international-corp/54-00174/12140150)|Audio Jack 3.5mm TRRS (2 Stereo channels and Microphone mono channel which is unused)
|[1792](https://www.digikey.com/en/products/detail/adafruit-industries-llc/1792/5774409)|Adafruit LED Sequins Pink
|[Teensy 4.0](https://www.sparkfun.com/teensy-4-0-headers.html)|Teensy 4.0 with Headers
|[Millmax 0531-0-15-15-31-27-10-0](https://www.digikey.com/en/products/detail/mill-max-manufacturing-corp/0531-0-15-15-31-27-10-0/4879975)|Pin receptacle connector for side Teensy pins|

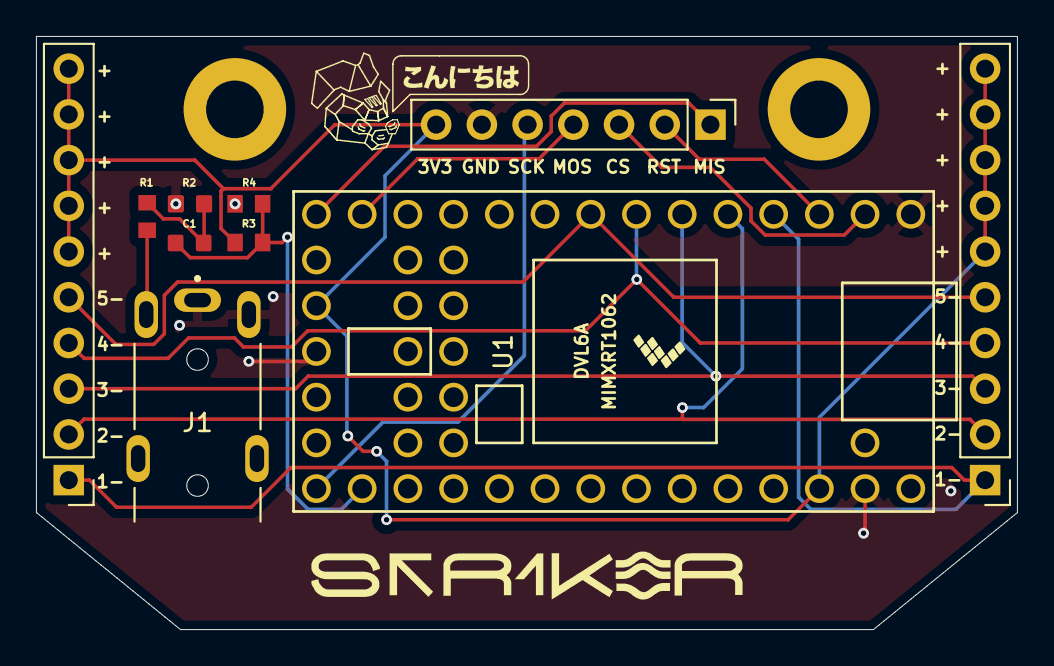
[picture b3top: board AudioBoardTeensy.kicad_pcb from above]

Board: 2 copper layers, 54.5 x 33.0 mm, 12 parts (0 on the bottom side), 15 nets.

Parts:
C1: 10uF; CL10A106KP8NNNC
H1, H2: MountingHole_Pad; MountingHole_3.2mm_M3_ISO7380_Pad
J1: 54-00174
J2, J3: Conn_01x10_Pin; PinHeader_1x10_P2.54mm_Vertical
J4: DFR0934; PinHeader_1x07_P2.54mm_Vertical
R1: 1K; RCG06031K00FKEA
R2: 2K; 0603WAF2001T5E
R3, R4: 100K; CRCW0603100KFKEA
U1: Teensy4.0; Teensy40

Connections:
+3V3: J2.6, J2.7, J2.8, J2.9, J2.10, J3.6, J3.7, J3.8, J3.9, J3.10, J4.7, R3.2, U1.16 (3V3), U1.31 (3V3)
A0: C1.1, R3.1, R4.2, U1.21 (14_A0_TX3_SPDIF_OUT)
AUDIO: J1.2, R1.2
CS: J4.3, U1.2 (0_RX1_CRX2_CS1)
GND: J1.1, J1.3, J4.6, R2.1, R4.1, U1.1 (GND), U1.17 (GND), U1.32 (GND)
LED1: J2.1, J3.1, U1.4 (2_OUT2)
LED2: J2.2, J3.2, U1.5 (3_LRCLK2)
LED3: J2.3, J3.3, U1.6 (4_BCLK2)
LED4: J2.4, J3.4, U1.7 (5_IN2)
LED5: J2.5, J3.5, U1.8 (6_OUT1D)
MISO: J4.1, U1.14 (12_MISO_MQSL)
MOSI: J4.4, U1.13 (11_MOSI_CTX1)
unnamed: C1.2, R1.1, R2.2
RST: J4.2, U1.3 (1_TX1_CTX2_MISO1)
SCK: J4.5, U1.20 (13_SCK_CRX1_LED)
